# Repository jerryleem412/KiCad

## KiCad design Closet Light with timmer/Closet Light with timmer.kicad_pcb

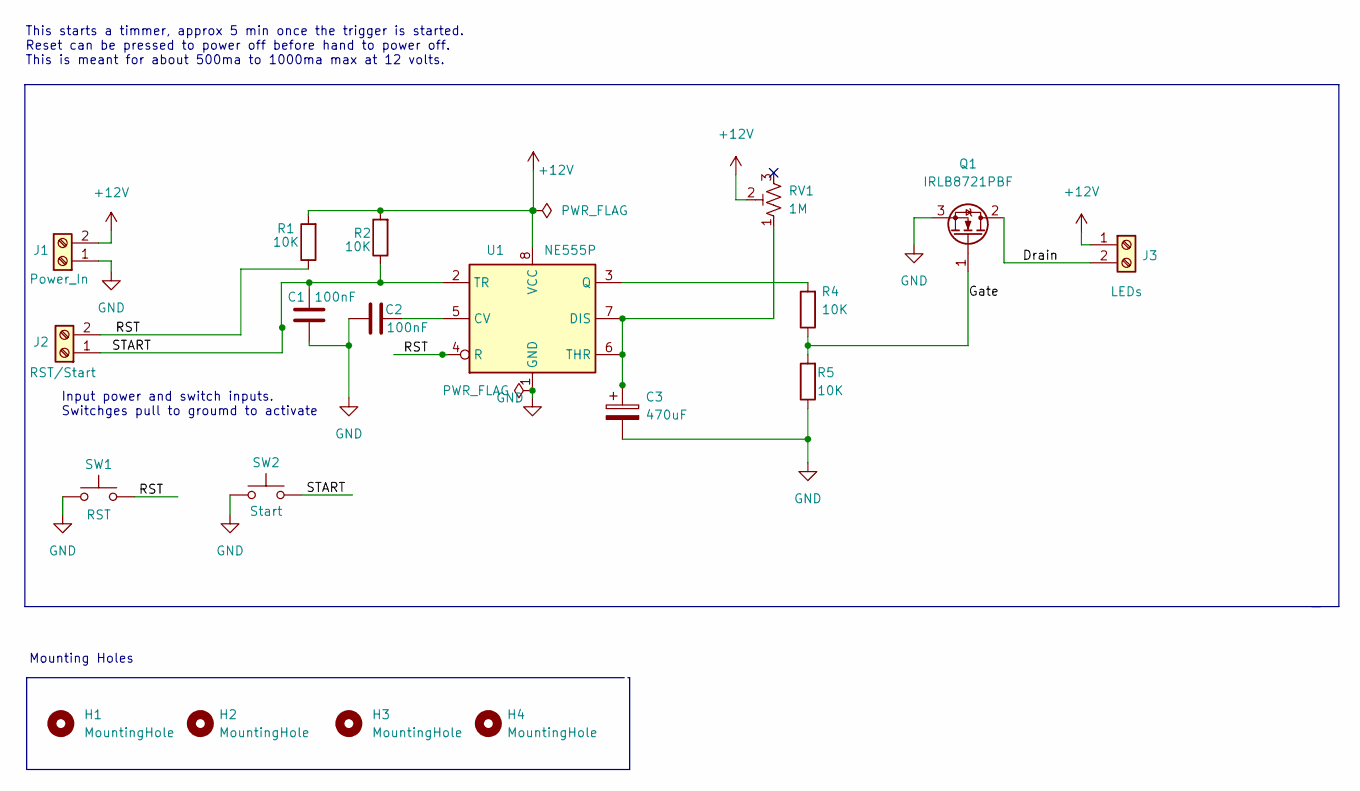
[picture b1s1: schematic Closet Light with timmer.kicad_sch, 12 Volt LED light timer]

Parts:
C1, C2: 100nF; C_Disc_D6.0mm_W2.5mm_P5.00mm
C3: 470uF; CP_Radial_D8.0mm_P5.00mm
H1, H2, H3, H4: MountingHole; MountingHole_2.2mm_M2_DIN965_Pad_TopBottom
J1: Power_In; TerminalBlock_Philmore_TB132_1x02_P5.00mm_Horizontal
J2: RST/Start; TerminalBlock_Philmore_TB132_1x02_P5.00mm_Horizontal
J3: LEDs; TerminalBlock_Philmore_TB132_1x02_P5.00mm_Horizontal
Q1: IRLB8721PBF; TO-220-3_Vertical
R1, R2, R4, R5: 10K; R_Axial_DIN0207_L6.3mm_D2.5mm_P7.62mm_Horizontal
RV1: 1M; Potentiometer_Bourns_3386F_Vertical
SW1: RST; SW_PUSH_6mm
SW2: Start; SW_PUSH_6mm
U1: NE555P; DIP-8_W7.62mm

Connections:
+12V: J1.2, J3.1, R1.2, R2.2, RV1.2, U1.8 (VCC)
/Drain: J3.2, Q1.2 (D)
/Gate: Q1.1 (G), R4.1, R5.2
/RST: J2.2, R1.1, SW1.2, U1.4 (R)
/START: C1.1, J2.1, R2.1, SW2.2, U1.2 (TR)
GND: C1.2, C2.1, C3.2, J1.1, Q1.3 (S), R5.1, SW1.1, SW2.1, U1.1 (GND)
unnamed: C2.2, U1.5 (CV)
unnamed: C3.1, RV1.1, U1.6 (THR), U1.7 (DIS)
unnamed: R4.2, U1.3 (Q)

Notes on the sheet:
Mounting Holes
This starts a timmer, approx 5 min once the trigger is started. Reset can be pressed to power off before hand to power off. This is meant for about 500ma to 1000ma max at 12 volts.
Input power and switch inputs. Switchges pull to groumd to activate

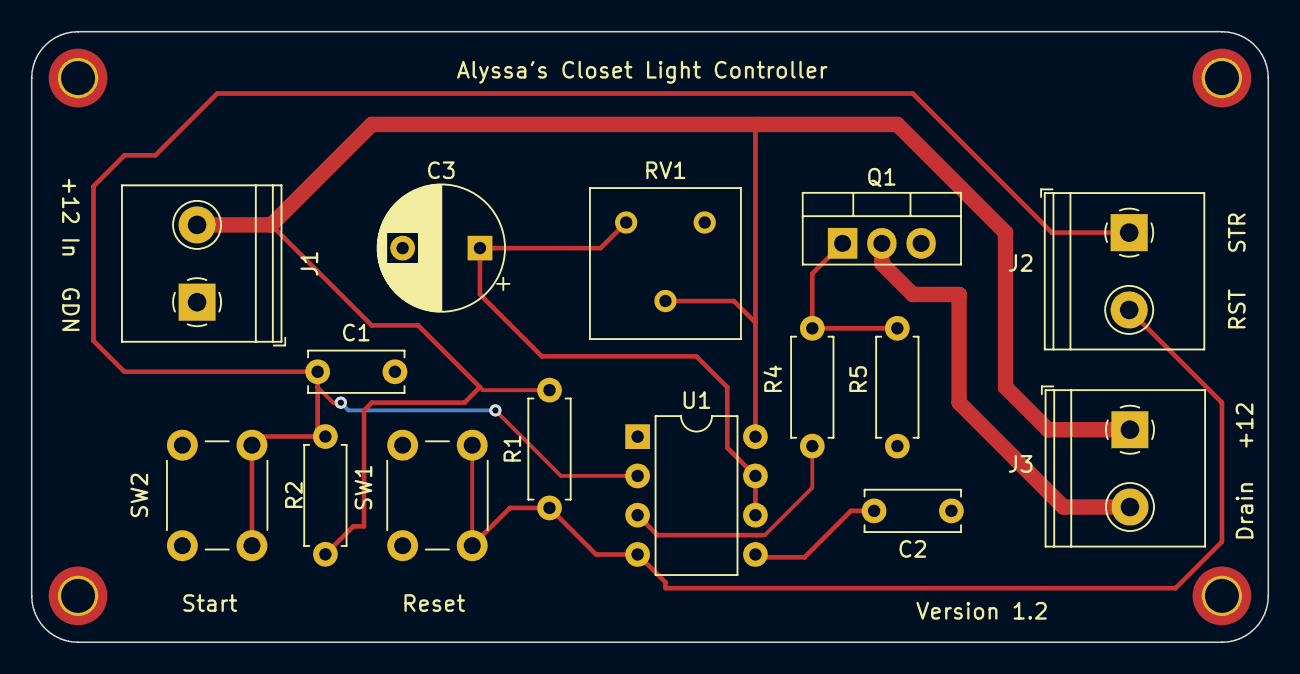
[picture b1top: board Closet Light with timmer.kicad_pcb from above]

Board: 2 copper layers, 80.0 x 39.5 mm, 19 parts (0 on the bottom side), 9 nets.

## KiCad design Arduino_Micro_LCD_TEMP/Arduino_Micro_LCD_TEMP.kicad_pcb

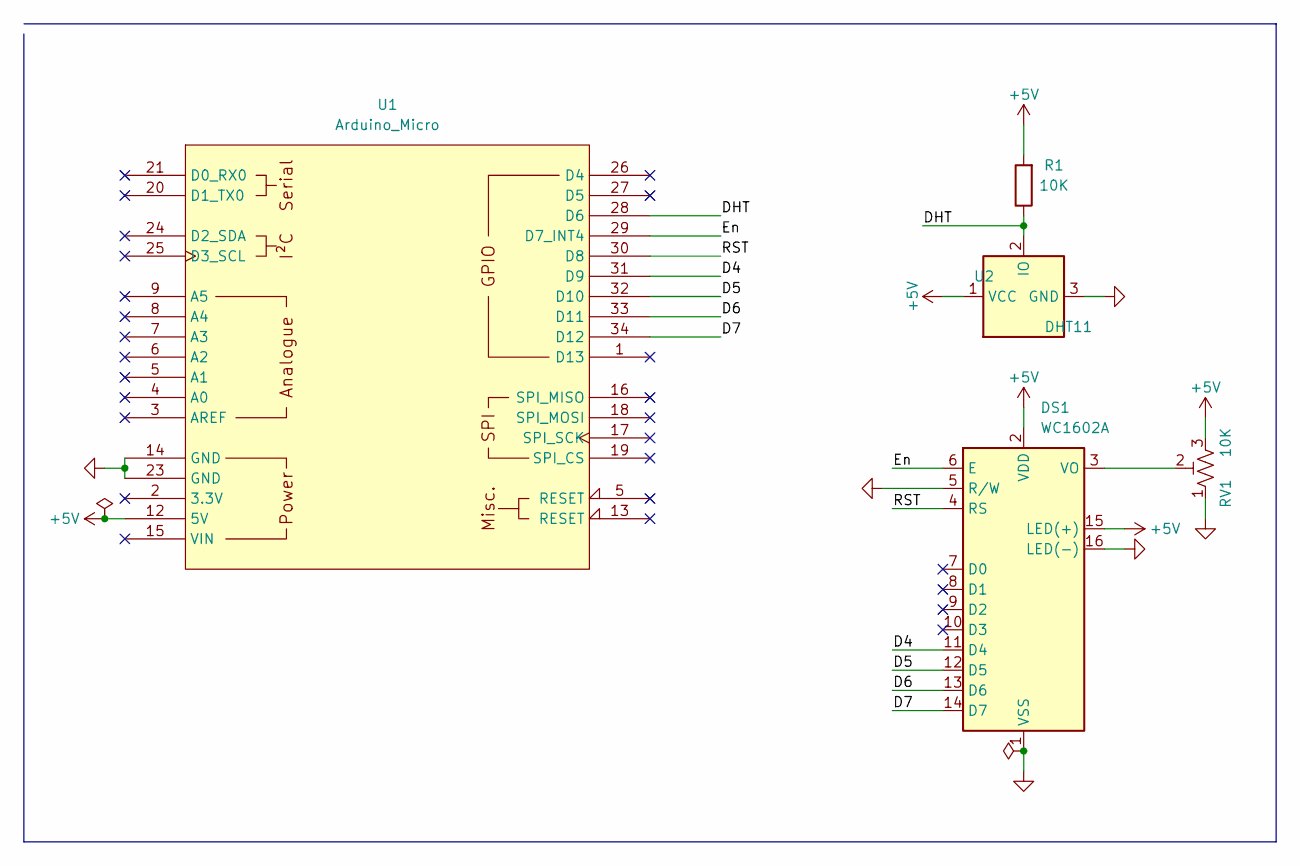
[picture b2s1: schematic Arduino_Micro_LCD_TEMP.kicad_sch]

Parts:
DS1: WC1602A
R1: 10K; R_Axial_DIN0207_L6.3mm_D2.5mm_P10.16mm_Horizontal
RV1: 10K; Potentiometer_ACP_CA9-H2,5_Horizontal
U1: Arduino_Micro; ARDUINO_Micro
U2: DHT11; PinHeader_1x03_P2.54mm_Vertical

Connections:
+5V: DS1.2 (VDD), DS1.15 (LED(+)), R1.2, RV1.3, U1.12 (5V), U2.1 (VCC)
/D4: DS1.11 (D4), U1.31 (D9)
/D5: DS1.12 (D5), U1.32 (D10)
/D6: DS1.13 (D6), U1.33 (D11)
/D7: DS1.14 (D7), U1.34 (D12)
/DHT: R1.1, U1.28 (D6), U2.2 (IO)
/En: DS1.6 (E), U1.29 (D7_INT4)
/RST: DS1.4 (RS), U1.30 (D8)
GND: DS1.1 (VSS), DS1.5 (R/W), DS1.16 (LED(-)), RV1.1, U1.14 (GND), U1.23 (GND), U2.3 (GND)
unnamed: DS1.3 (VO), RV1.2

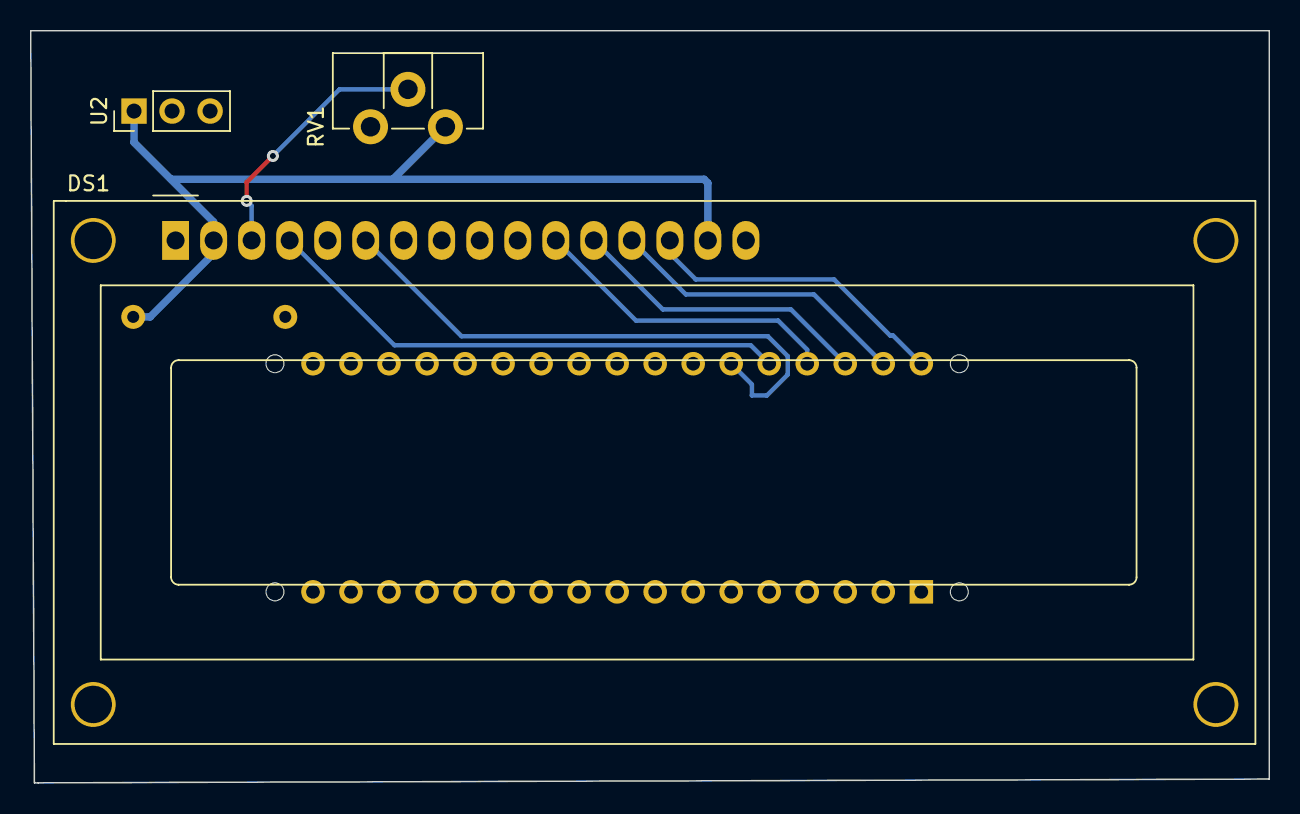
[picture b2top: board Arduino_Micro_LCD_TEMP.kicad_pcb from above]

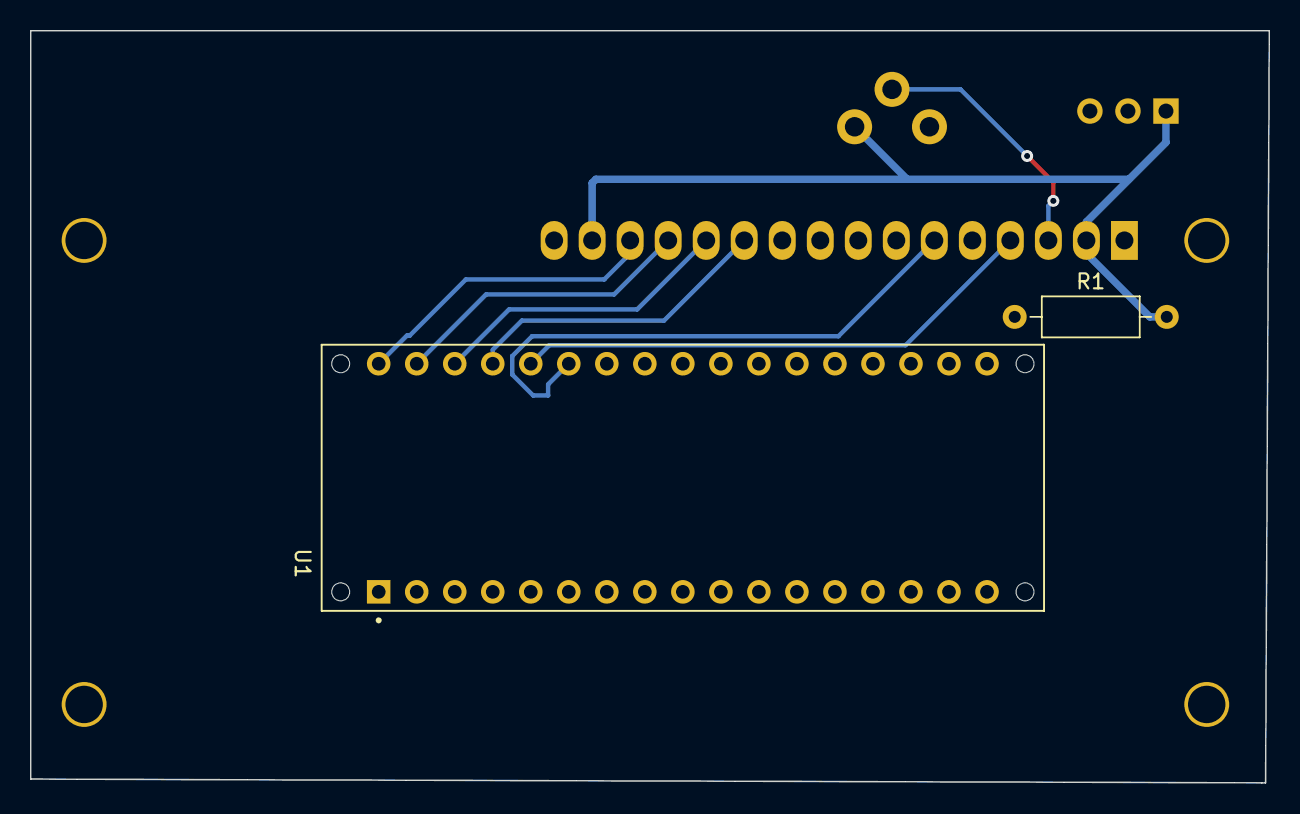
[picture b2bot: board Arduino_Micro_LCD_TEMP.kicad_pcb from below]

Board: 2 copper layers, 82.8 x 50.2 mm, 5 parts (2 on the bottom side), 10 nets.

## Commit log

2022-12-23 init
2022-12-23 Updated 3D models
